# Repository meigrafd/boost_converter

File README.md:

booster
=======

A boost converter Addon for Nathan Chantrell's TinyTX to extend battery life: https://github.com/nathanchantrell/TinyTX/

<br>

Its my first PCB so please be lenient :)

##License
Proudly open source<br>
The hardware designs (schematics and CAD files) are licensed under a Creative Commons Attribution-ShareAlike 3.0 Unported License.<br>
The documentation is subject to GNU Free Documentation License<br>

##Overview
The board uses an ultra low-drain LTC3525 boost regulator chip which draws only 7..30 µA in idle mode (depends on input voltage). The input can range from 1.0V to 5.5V (absolute maximum: 6V), so this can also be used with 2x or 3x AA battery packs (even 4, if NiMh). The regulator continues to operate with input voltage fading to less than 0.5V - squeezing the last bit of energy from the battery.

The board was specifically designed for use with a TinyTX, but can be used with anything that needs 3.3V. The maximum output current is 60..150 mA, depending on input voltage.

Taking a reading once every 60s the TinyTX batteries should last for 1-3 years. I recommend rechargeable alkaline batteries for best performance and environmental impact.

The PCB has a size of: 13.2mm x 11.0mm

========
German
========

Das PCB besteht aus 2 Layers:  Top (rot) und Bottom (blau)<br>
Wenn man normalerweise ein Board in Eagle öffnet wird die Polygon Fläche nicht angezeigt - was bei mir auf dem Screenshot aber der Fall ist, deshalb ist auch fast das ganze Board mit Rot auf der Oberseite und Blau auf der Unterseite ausgefüllt... Diese Polygon Fläche (Kupfer) wird einerseits zur Kühlung genutzt, anderseits für GND und zusätzlich muss beim Herstellungsprozess weniger Kupfer weggeätzt werden - deshalb sind die unteren beiden GND Löt-Pads auch nicht extra verdrahtet, sondern eben mit beiden Polygon Flächen verbunden. 

Beschriftungen auf der Oberseite:
* Oben rechts ist das "Open Hardware" Logo.
* Unten rechts ist ein "boost converter" Schriftzug.
* Die Bauteile "L1" mit 10uH , "C1" mit 1uF und "C2" mit 10uF

Beschriftungen auf der Unterseite: (gespiegelt)
* Die Lötbohrungen für die Messung der Batteriespannung: BAT state
* Die Lötbohrungen für die Batterie: Vin und GND
* Die Lötbohrungen für die TinyTX Platine: GND und Vout
* Oben hab ich mir erlaubt einen Zweizeiler zu setzen:<br>
 TinyTX boost converter v1.0<br>
 http://forum-raspberrypi.de

Ich werd jetzt versuchen jemanden zu finden der das PCB nochmal prüft (wenn hier jmd is bitte bei mir melden) und dann erste Prototype PCB's anfertigen lassen - mal gucken ob das so funktioniert :-)

**Hintergrund:**<br>
Der LTC3525 boost regulator chip verbraucht sehr wenig Strom: 7 bis 30 µA im idle mode (kommt auf die Input Voltage an) und kann mit einer Spannung zwischen 1.0 und 5.5V umgehen. Man kann also auch problemlos 3xAA Alkaline (oder 4 x NiMh) Batterien benutzen.<br>
Ausserdem arbeitet der Boost Converter auch noch bei einer Spannung von nur 0.5V weiter, es wird also wirklich das letzte Quentchen aus den Batterien gelutscht ;)<br>
http://jeelabs.net/projects/hardware/wiki/AA_Power_Board haben ebenfalls ein PCB entwickelt wo der LTC3525 zum Einsatz kommt und auch OpenEnergyMonitor verwenden den LTC3525 mit ihren http://wiki.openenergymonitor.org/index.php?title=EmonTH Funk Sensoren.

PS: Ein gutes Tutorial für Eagle, was mir sehr geholfen hat: http://service.projektlabor.tu-berlin.de/onlinekurs/eagleboard/

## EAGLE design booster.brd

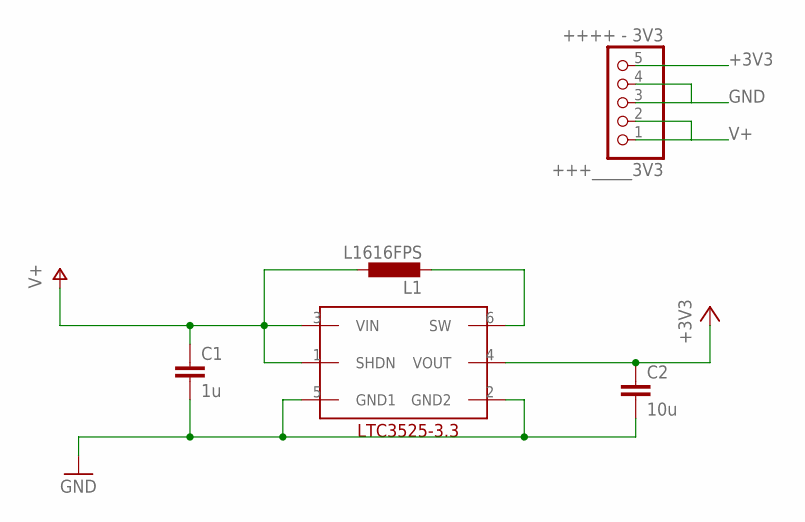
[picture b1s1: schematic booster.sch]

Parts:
+++_____3V3: ++++ - 3V3; 1X05
C1: 1u; C0805
C2: 10u; C0805
IC: LTC3525; TSOT23-6
L1: L1616FPS; L1616

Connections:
+3V3: +++_____3V3.5, C2.1, IC.4 (VOUT)
GND: +++_____3V3.3, +++_____3V3.4, C1.2, C2.2, IC.2 (GND2), IC.5 (GND1)
unnamed: IC.6 (SW), L1.P$2 (2)
V+: +++_____3V3.1, +++_____3V3.2, C1.1, IC.1 (SHDN), IC.3 (VIN), L1.P$1 (1)

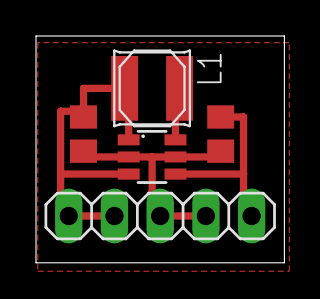
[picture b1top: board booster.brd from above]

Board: 2 copper layers, 13.8 x 12.6 mm, 5 parts (0 on the bottom side), 4 nets.

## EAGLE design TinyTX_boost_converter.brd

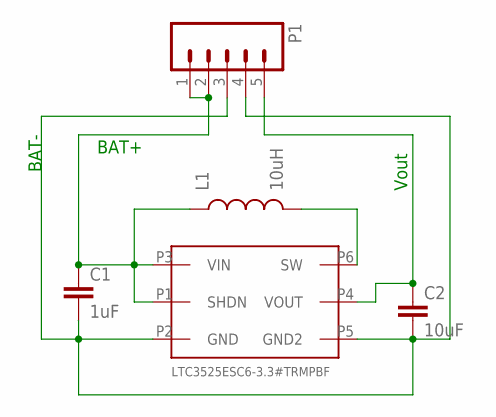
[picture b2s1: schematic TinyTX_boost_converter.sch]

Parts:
C1: 1uF; 0603-CAP
C2: 10uF; 0603-CAP
L1: 10uH; 1210
P1: M05PTH; 1X05
U1: LTC3525; 6-LEAD-SC70

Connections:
GND: C1.2, C2.2, P1.3, P1.4, U1.P2 (GND), U1.P5 (GND2)
P6: L1.2, U1.P6 (SW)
VCC: C2.1, P1.5, U1.P4 (VOUT)
VIN: C1.1, L1.1, P1.1, P1.2, U1.P1 (SHDN), U1.P3 (VIN)

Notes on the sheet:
Vout
LTC3525ESC6-3.3#TRMPBF
BAT+
BAT-

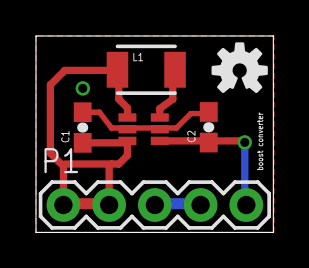
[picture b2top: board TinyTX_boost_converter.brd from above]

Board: 2 copper layers, 13.2 x 10.9 mm, 6 parts (0 on the bottom side), 4 nets.

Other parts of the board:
U$1: OSHW-LOGO-S

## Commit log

2014-01-26 First Build
2014-01-26 Added Part List
2014-03-07 Final Build

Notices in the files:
parts and their libraries:
SparkFun-Capacitors: Licensing: CC v3.0 Share-Alike You are welcome to use this library for commercial purposes.
